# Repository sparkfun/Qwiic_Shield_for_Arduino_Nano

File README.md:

SparkFun Qwiic Shield for Arduino Nano
========================================

[*SparkFun Qwiic Shield for Arduino Nano (DEV-16130)*](https://www.sparkfun.com/products/16130)

This is a shield that connects the I<sup>2</sup>C bus of an Arduino Nano (or compatible board) to four Qwiic connectors.

Repository Contents
-------------------

* **/Hardware** - Eagle design files (.brd, .sch)
* **/Production** - Production panel files (.brd)

Documentation
--------------

* **[Hookup Guide](https://learn.sparkfun.com/tutorials/sparkfun-qwiic-shield-for-arduino-nano-hookup-guide)** - Basic hookup guide for the Qwiic Shield for Arduino Nano.
* **[SparkFun Fritzing repo](https://github.com/sparkfun/Fritzing_Parts)** - Fritzing diagrams for SparkFun products.
* **[SparkFun 3D Model repo](https://github.com/sparkfun/3D_Models)** - 3D models of SparkFun products. 
* **[SparkFun Graphical Datasheets](https://github.com/sparkfun/Graphical_Datasheets)** -Graphical Datasheets for various SparkFun products.

Product Versions
----------------

* [DEV-16130](https://www.sparkfun.com/products/16130)- An Arduino shield to connect the I<sup>2</sup>C bus on an Arduino Nano (or compatible board) to Qwiic connectors. 

License Information
-------------------

This product is _**open source**_! 

Please review the LICENSE.md file for license information. 

If you have any questions or concerns on licensing, please contact technical support on our [SparkFun forums](https://forum.sparkfun.com/viewforum.php?f=152).

Distributed as-is; no warranty is given.

- Your friends at SparkFun.

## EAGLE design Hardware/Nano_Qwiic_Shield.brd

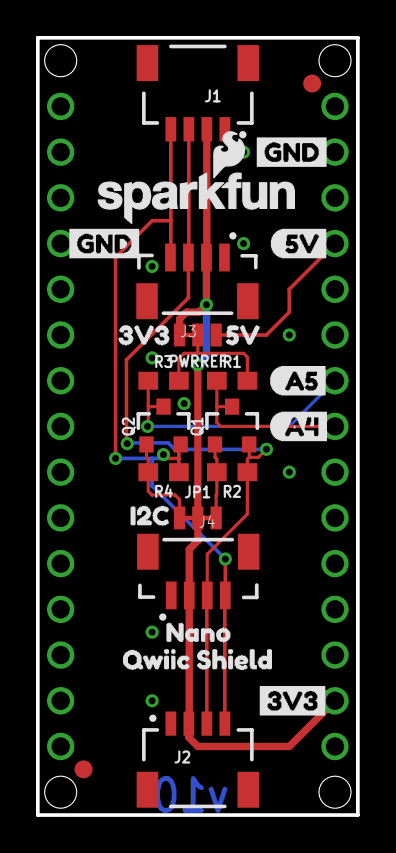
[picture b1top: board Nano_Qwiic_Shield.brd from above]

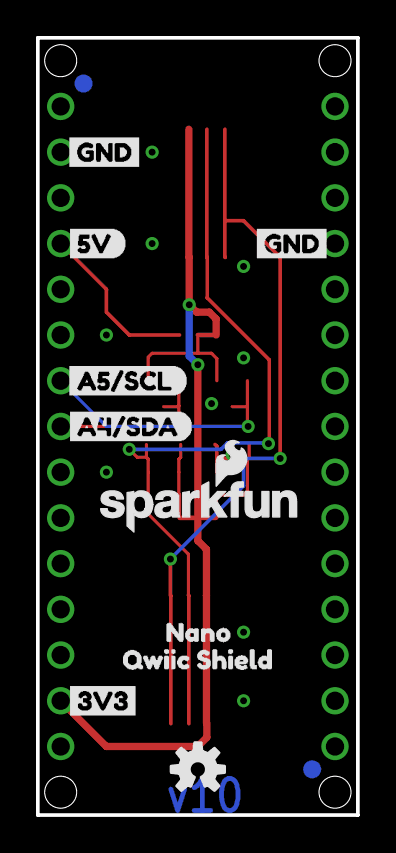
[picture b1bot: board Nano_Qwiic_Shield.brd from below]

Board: 2 copper layers, 17.8 x 43.2 mm, 40 parts (12 on the bottom side), 10 nets.

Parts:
FD1, FD2, FD3, FD4: FIDUCIAL1X2; FIDUCIAL-1X2
FRAME1: FRAME-LETTER; CREATIVE_COMMONS
J1, J2: QWIIC_RIGHT_ANGLE; JST04_1MM_RA
J3, J4: Vertical Qwiic Connector; JST04_1MM_VERT
J5: NANO_FOOTPRINT; NANO
JP1: JUMPER-SMT_3_2-NC_TRACE_NO-SILK; SMT-JUMPER_3_2-NC_TRACE_NO-SILK
LOGO1: OSHW-LOGOS; OSHW-LOGO-S
LOGO2, LOGO3: SFE_LOGO_NAME_FLAME.1_INCH; SFE_LOGO_NAME_FLAME_.1
PWRREF: JUMPER-SMT_3_1-NC_TRACE_NO-SILK; SMT-JUMPER_3_1-NC_TRACE_NO-SILK
Q1, Q2: 220mA/50V/3.5Ω; SOT23-3
R1, R2, R3, R4: 4.7k; 0603
U$1, U$15: QWIIC_SHIELD1
U$2, U$14: NANO1
U$3: A4#SDA5
U$4: A5#SCL4
U$5, U$6, U$7, U$8: GND0
U$9: A45
U$10: A56
U$11: I2C6
U$12, U$13: 3V36
U$16: 3V31
U$17, U$18: 5V0
U$19: 5V1

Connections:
3.3V: J1.2, J2.2, J3.2, J4.2, J5.17, JP1.2, PWRREF.3
5V: J5.27, PWRREF.1
GND: J1.1, J2.1, J3.1, J4.1, J5.4, J5.29
HV_SCL: J5.24, Q2.3, R3.1
HV_SDA: J5.23, Q1.3, R1.1
IOREF: PWRREF.2, R1.2, R3.2
SCL: J1.4, J2.4, J3.4, J4.4, Q2.2, R4.1
SCLJUMP: JP1.1, Q2.1, R4.2
SDA: J1.3, J2.3, J3.3, J4.3, Q1.2, R2.1
SDAJUMP: JP1.3, Q1.1, R2.2

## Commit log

2019-12-11 Initial layout and commit
2019-12-16 Initial commit/run of checklist
2019-12-16 post review changes
2019-12-23 adding conversion circuitry
2019-12-23 adding production files
2020-01-29 Create README File
2020-01-29 Create .gitignore file
    Add gitignore file.
2020-01-29 Create LICENSE.md
    Creating License file.
2020-01-29 Create .gitattributes file
    Adding gitattributes file.
2020-01-29 removing .b## and .s##
2020-01-29 Rename Board File
2020-01-29 Rename Schematic file
2020-05-28 Update README
    Adding updated product photo and adjusting link to new product page.

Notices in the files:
parts and their libraries:
SparkFun-Aesthetics: Licensing: Creative Commons ShareAlike 4.0 International - https://creativecommons.org/licenses/by-sa/4.0
SparkFun-Aesthetics: Released under the Creative Commons Attribution Share-Alike 4.0 License
SparkFun-Aesthetics: https://creativecommons.org/licenses/by-sa/4.0
